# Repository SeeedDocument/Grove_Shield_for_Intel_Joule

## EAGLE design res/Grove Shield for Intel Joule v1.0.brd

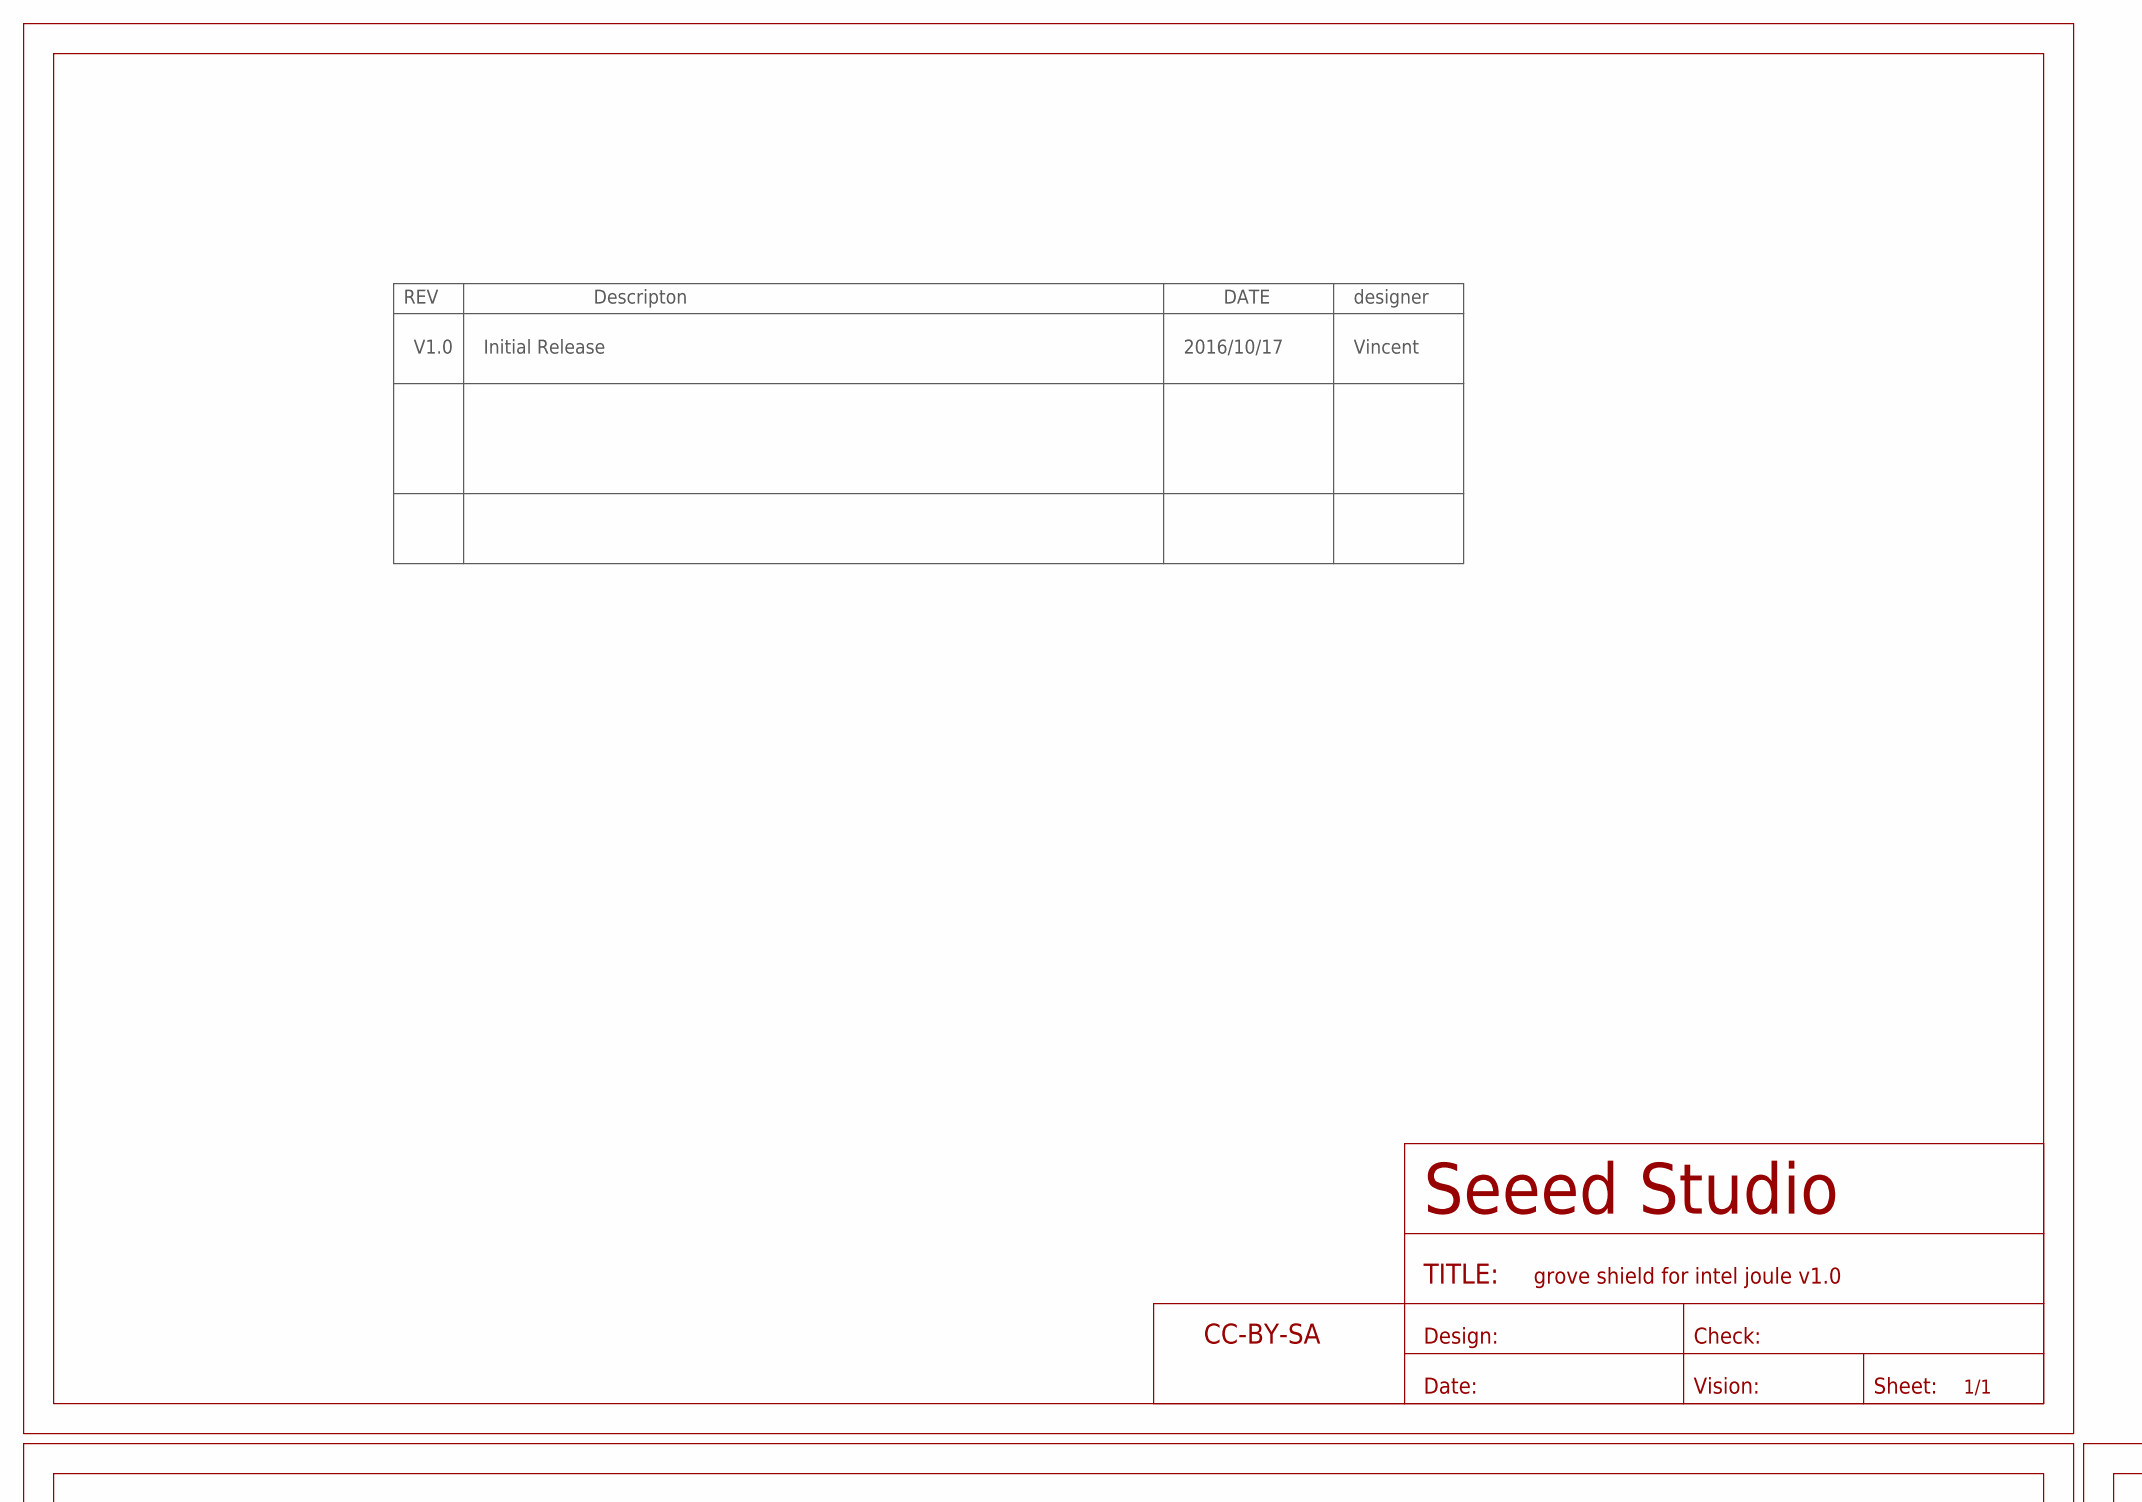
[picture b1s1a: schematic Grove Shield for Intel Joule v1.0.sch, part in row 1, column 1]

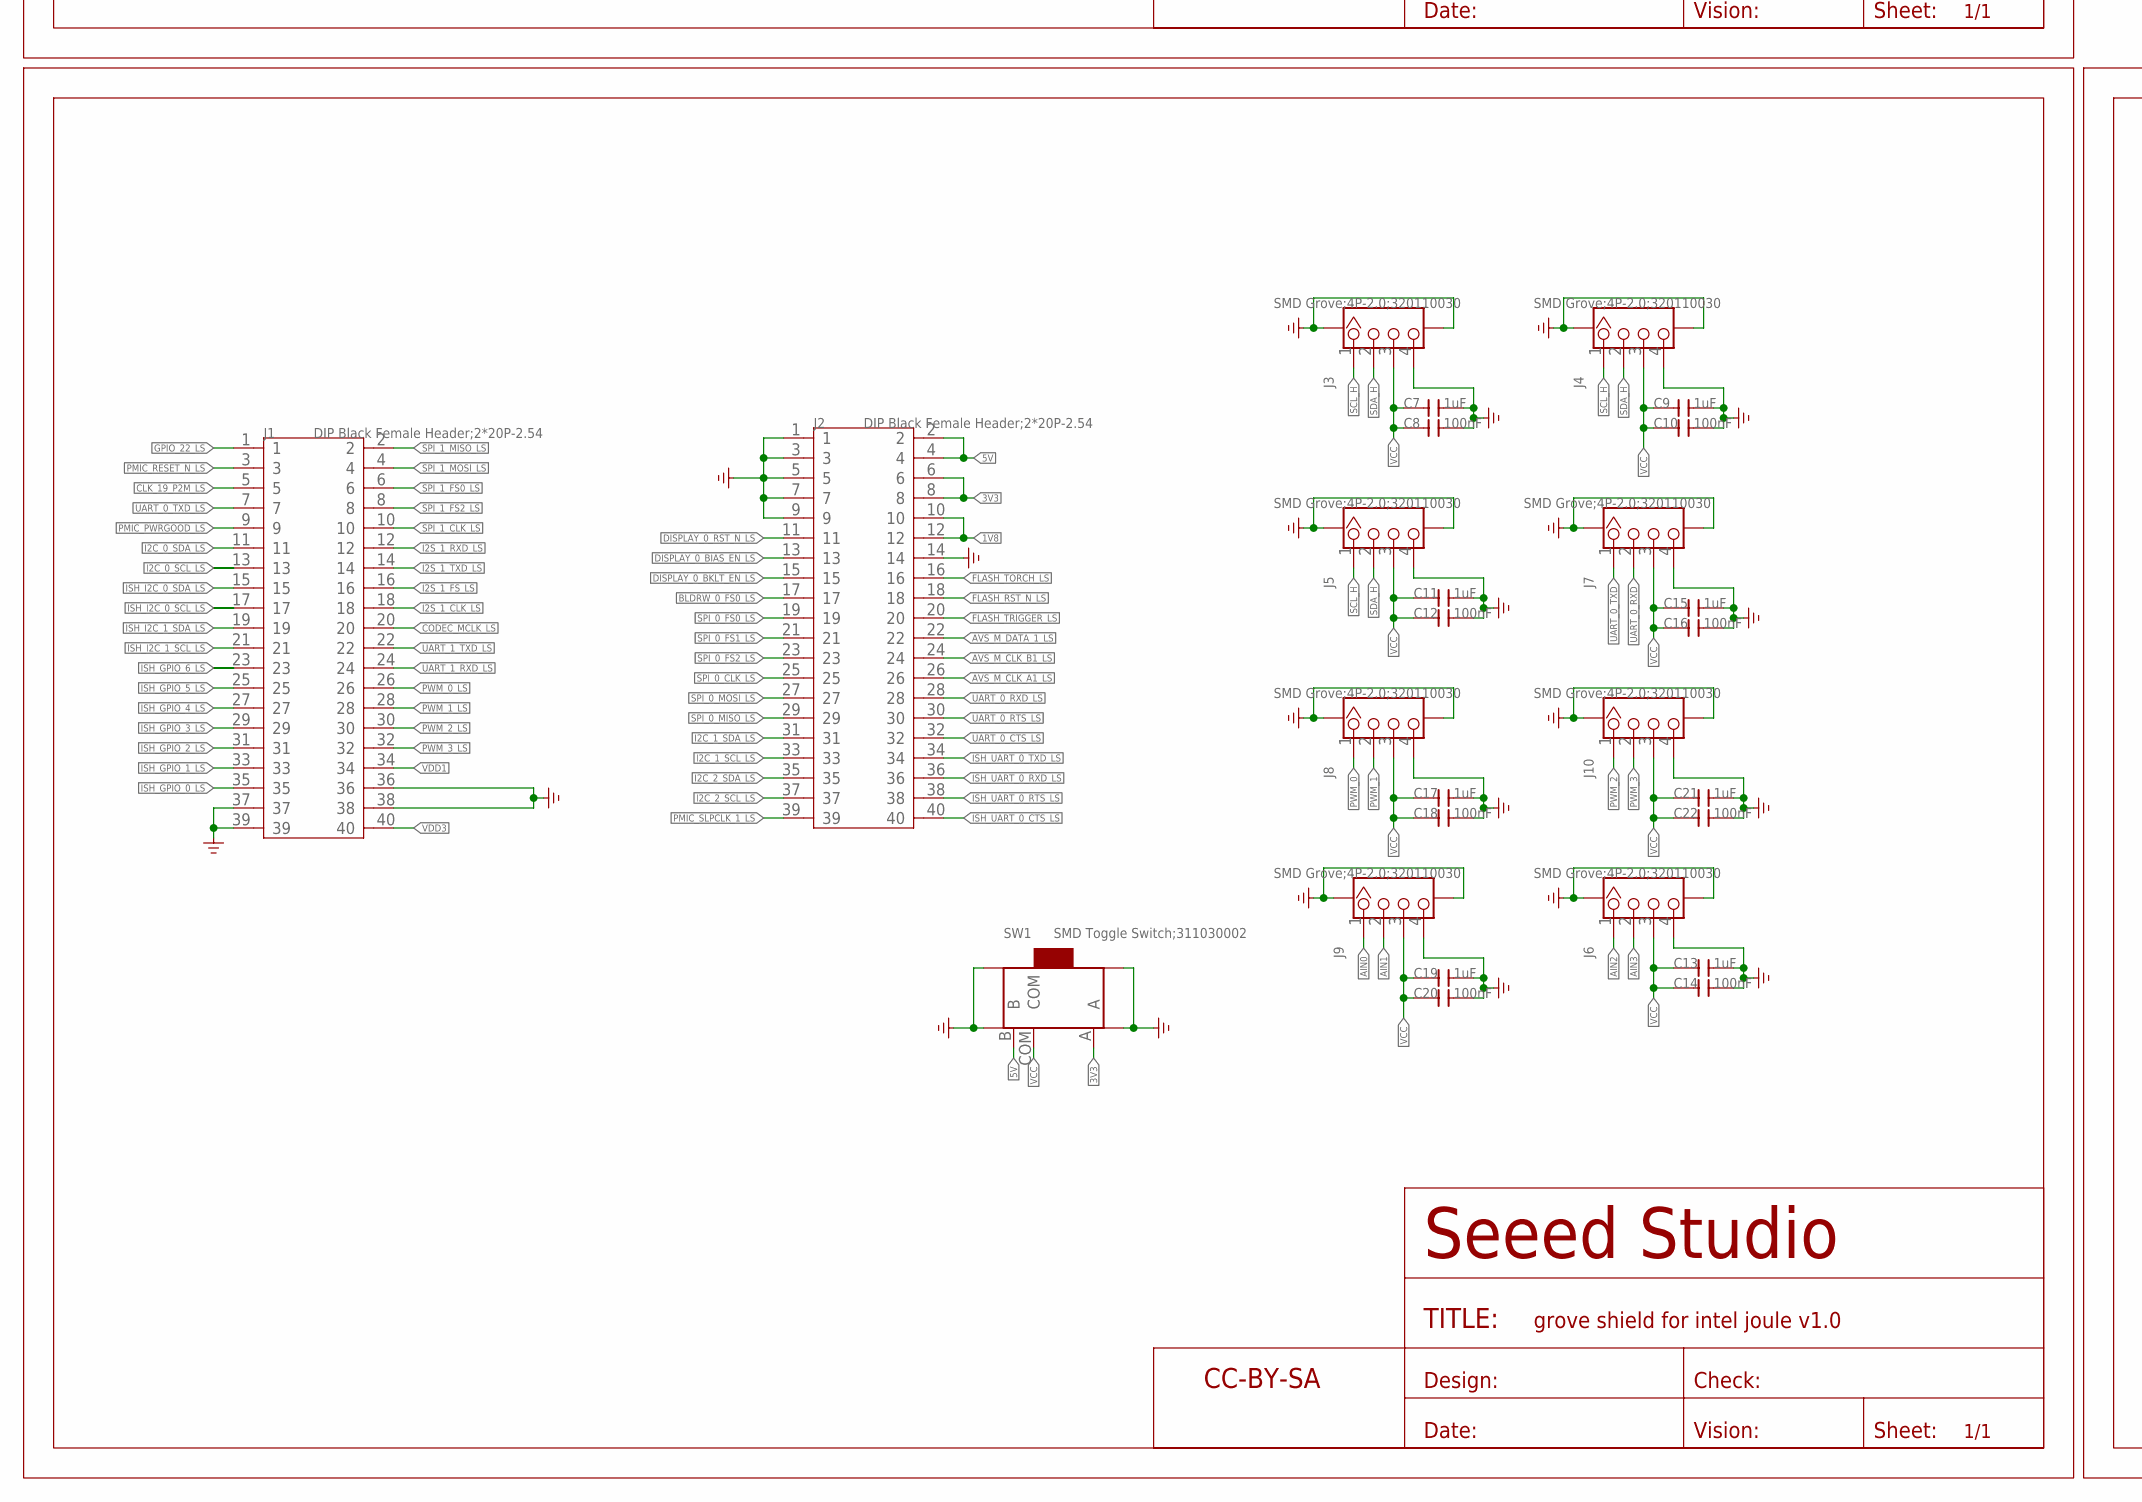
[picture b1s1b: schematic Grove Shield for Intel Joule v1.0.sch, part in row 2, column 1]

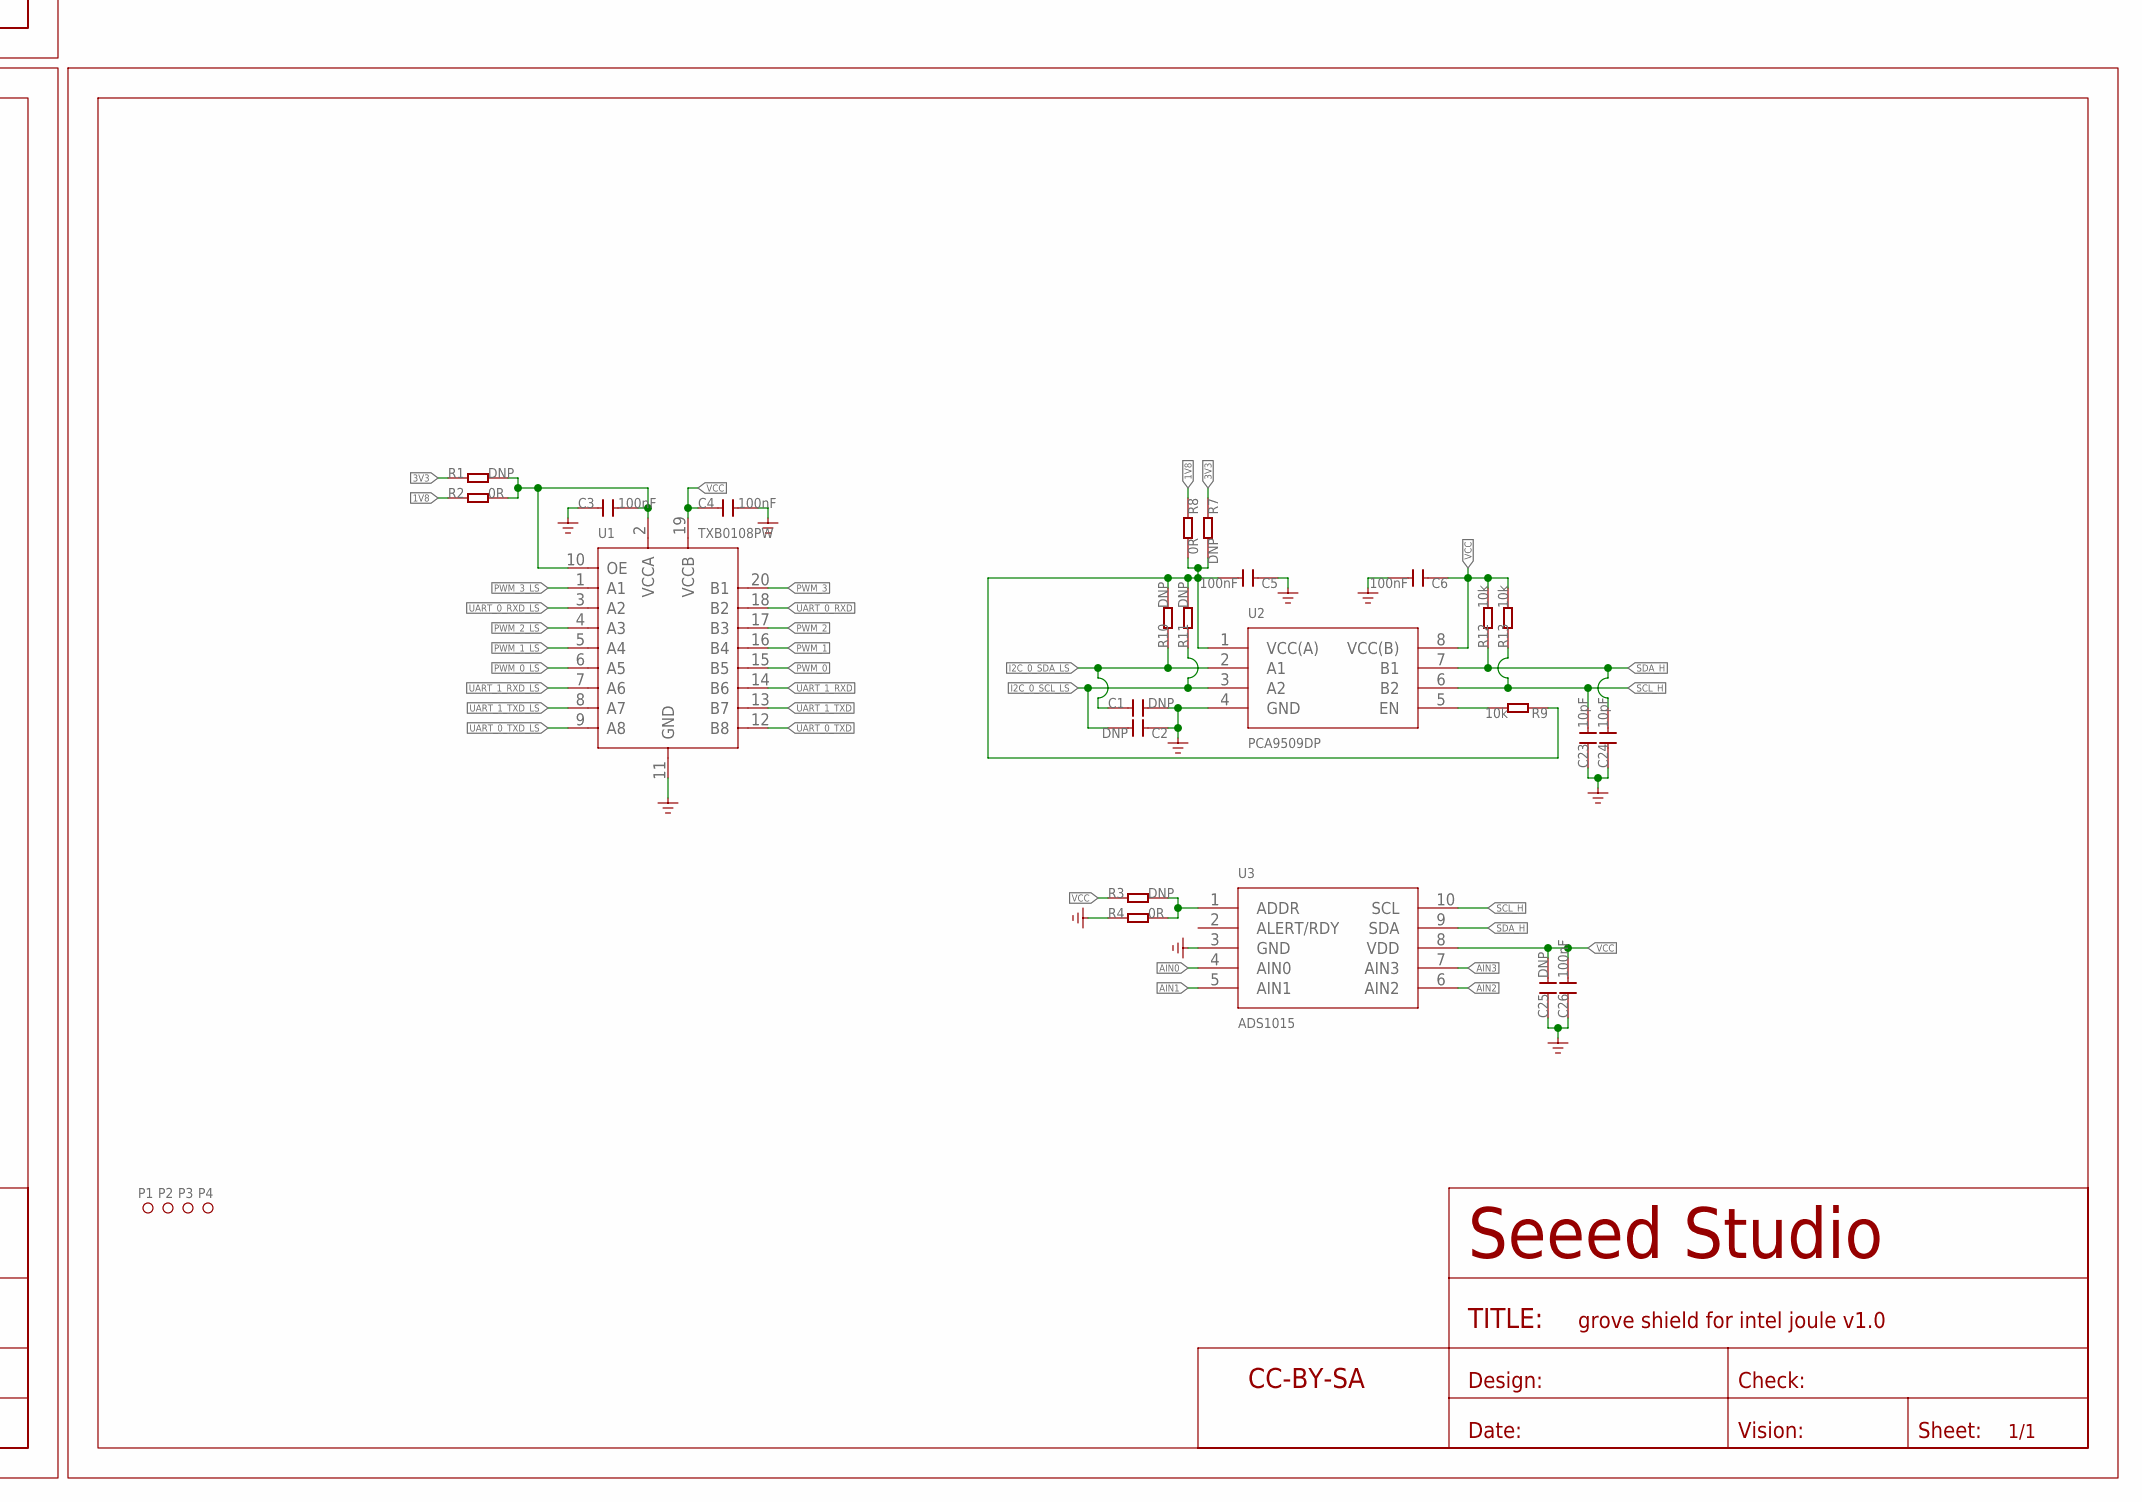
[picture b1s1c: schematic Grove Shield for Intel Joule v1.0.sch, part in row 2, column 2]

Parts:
C1, C2, C25: DNP; C0603
C3, C4, C5, C6, C8, C10, C12, C14, C16, C18, C20, C22, C26: 100nF; C0603
C7, C9, C11, C13, C15, C17, C19, C21: 1uF; C0603
C23, C24: 10pF; C0603
FR1, FR2, FR3: SEEEDSTUDIO-OPEN-SCH-FRAME; SEEEDSTUDIO-PCB-FRAME
J1, J2: DIP Black Female Header;2*20P-2.54; H2X20-2.54MM
J3, J4, J5, J6, J7, J8, J9, J10: SMD Grove;4P-2.0;320110030; HW4-SMD-2.0
P1, P2, P3, P4: MARK-1.0'ANNULAR'; ROUND-MARK-1.0
R1, R3, R7, R10, R11: DNP; R0603
R2, R4, R8: 0R; R0603
R9, R12, R13: 10k; R0603
SW1: SMD Toggle Switch;311030002; SW7-SMD-6.7X2.6X1.4MM-90D
U1: TXB0108PW; TSSOP20-0.65-6.5X4.4MM
U2: PCA9509DP; TSSOP8-0.65-3X3MM
U3: ADS1015; SSOP10-0.5-3X3MM

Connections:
1V8: J2.10, J2.12, R2.1, R8.1
3V3: J2.6, J2.8, R1.1, R7.1, SW1.A
5V: J2.2, J2.4, SW1.B
AIN0: J9.1, U3.4 (AIN0)
AIN1: J9.2, U3.5 (AIN1)
AIN2: J6.1, U3.6 (AIN2)
AIN3: J6.2, U3.7 (AIN3)
AVS_M_CLK_A1_LS: J2.26
AVS_M_CLK_B1_LS: J2.24
AVS_M_DATA_1_LS: J2.22
BLDRW_0_FS0_LS: J2.17
CLK_19_P2M_LS: J1.5
CODEC_MCLK_LS: J1.20
DISPLAY_0_BIAS_EN_LS: J2.13
DISPLAY_0_BKLT_EN_LS: J2.15
DISPLAY_0_RST_N_LS: J2.11
FLASH_RST_N_LS: J2.18
FLASH_TORCH_LS: J2.16
FLASH_TRIGGER_LS: J2.20
GND: C1.2, C2.1, C3.1, C4.2, C5.1, C6.2, C7.2, C8.2, C9.2, C10.2, C11.2, C12.2, C13.2, C14.2, C15.2, C16.2, C17.2, C18.2, C19.2, C20.2, C21.2, C22.2, C23.1, C24.1, C25.1, C26.1, J1.36, J1.37, J1.38, J1.39, J2.1, J2.3, J2.5, J2.7, J2.9, J2.14, J3.4, J3.SS1, J3.SS2, J4.4, J4.SS1, J4.SS2, J5.4, J5.SS1, J5.SS2, J6.4, J6.SS1, J6.SS2, J7.4, J7.SS1, J7.SS2, J8.4, J8.SS1, J8.SS2, J9.4, J9.SS1, J9.SS2, J10.4, J10.SS1, J10.SS2, R4.1, SW1.P1 (SS1), SW1.P2 (SS2), SW1.P3 (SS3), SW1.P4 (SS4), U1.11 (GND), U2.4 (GND), U3.3 (GND)
GPIO_22_LS: J1.1
I2C_0_SCL_LS: C2.2, J1.13, R11.1, U2.3 (A2)
I2C_0_SDA_LS: C1.1, J1.11, R10.1, U2.2 (A1)
I2C_1_SCL_LS: J2.33
I2C_1_SDA_LS: J2.31
I2C_2_SCL_LS: J2.37
I2C_2_SDA_LS: J2.35
I2S_1_CLK_LS: J1.18
I2S_1_FS_LS: J1.16
I2S_1_RXD_LS: J1.12
I2S_1_TXD_LS: J1.14
ISH_GPIO_0_LS: J1.35
ISH_GPIO_1_LS: J1.33
ISH_GPIO_2_LS: J1.31
ISH_GPIO_3_LS: J1.29
ISH_GPIO_4_LS: J1.27
ISH_GPIO_5_LS: J1.25
ISH_GPIO_6_LS: J1.23
ISH_I2C_0_SCL_LS: J1.17
ISH_I2C_0_SDA_LS: J1.15
ISH_I2C_1_SCL_LS: J1.21
ISH_I2C_1_SDA_LS: J1.19
ISH_UART_0_CTS_LS: J2.40
ISH_UART_0_RTS_LS: J2.38
ISH_UART_0_RXD_LS: J2.36
ISH_UART_0_TXD_LS: J2.34
unnamed: R9.2, U2.5 (EN)
unnamed: R3.2, R4.2, U3.1 (ADDR)
unnamed: C5.2, R7.2, R8.2, R9.1, R10.2, R11.2, U2.1 (VCC(A))
unnamed: C3.2, R1.2, R2.2, U1.2 (VCCA), U1.10 (OE)
PMIC_PWRGOOD_LS: J1.9
PMIC_RESET_N_LS: J1.3
PMIC_SLPCLK_1_LS: J2.39
PWM_0: J8.1, U1.15 (B5)
PWM_0_LS: J1.26, U1.6 (A5)
PWM_1: J8.2, U1.16 (B4)
PWM_1_LS: J1.28, U1.5 (A4)
PWM_2: J10.1, U1.17 (B3)
PWM_2_LS: J1.30, U1.4 (A3)
PWM_3: J10.2, U1.20 (B1)
PWM_3_LS: J1.32, U1.1 (A1)
SCL_H: C23.2, J3.1, J4.1, J5.1, R13.1, U2.6 (B2), U3.10 (SCL)
SDA_H: C24.2, J3.2, J4.2, J5.2, R12.1, U2.7 (B1), U3.9 (SDA)
SPI_0_CLK_LS: J2.25
SPI_0_FS0_LS: J2.19
SPI_0_FS1_LS: J2.21
SPI_0_FS2_LS: J2.23
SPI_0_MISO_LS: J2.29
SPI_0_MOSI_LS: J2.27
SPI_1_CLK_LS: J1.10
SPI_1_FS0_LS: J1.6
SPI_1_FS2_LS: J1.8
SPI_1_MISO_LS: J1.2
SPI_1_MOSI_LS: J1.4
UART_0_CTS_LS: J2.32
UART_0_RTS_LS: J2.30
UART_0_RXD: J7.2, U1.18 (B2)
UART_0_RXD_LS: J2.28, U1.3 (A2)
UART_0_TXD: J7.1, U1.12 (B8)
UART_0_TXD_LS: J1.7, U1.9 (A8)
UART_1_RXD: U1.14 (B6)
UART_1_RXD_LS: J1.24, U1.7 (A6)
UART_1_TXD: U1.13 (B7)
UART_1_TXD_LS: J1.22, U1.8 (A7)
VCC: C4.1, C6.1, C7.1, C8.1, C9.1, C10.1, C11.1, C12.1, C13.1, C14.1, C15.1, C16.1, C17.1, C18.1, C19.1, C20.1, C21.1, C22.1, C25.2, C26.2, J3.3, J4.3, J5.3, J6.3, J7.3, J8.3, J9.3, J10.3, R3.1, R12.2, R13.2, SW1.COM, U1.19 (VCCB), U2.8 (VCC(B)), U3.8 (VDD)
VDD1: J1.34
VDD3: J1.40

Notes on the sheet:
REV
Descripton
DATE
designer
V1.0
Initial Release
2016/10/17
Vincent

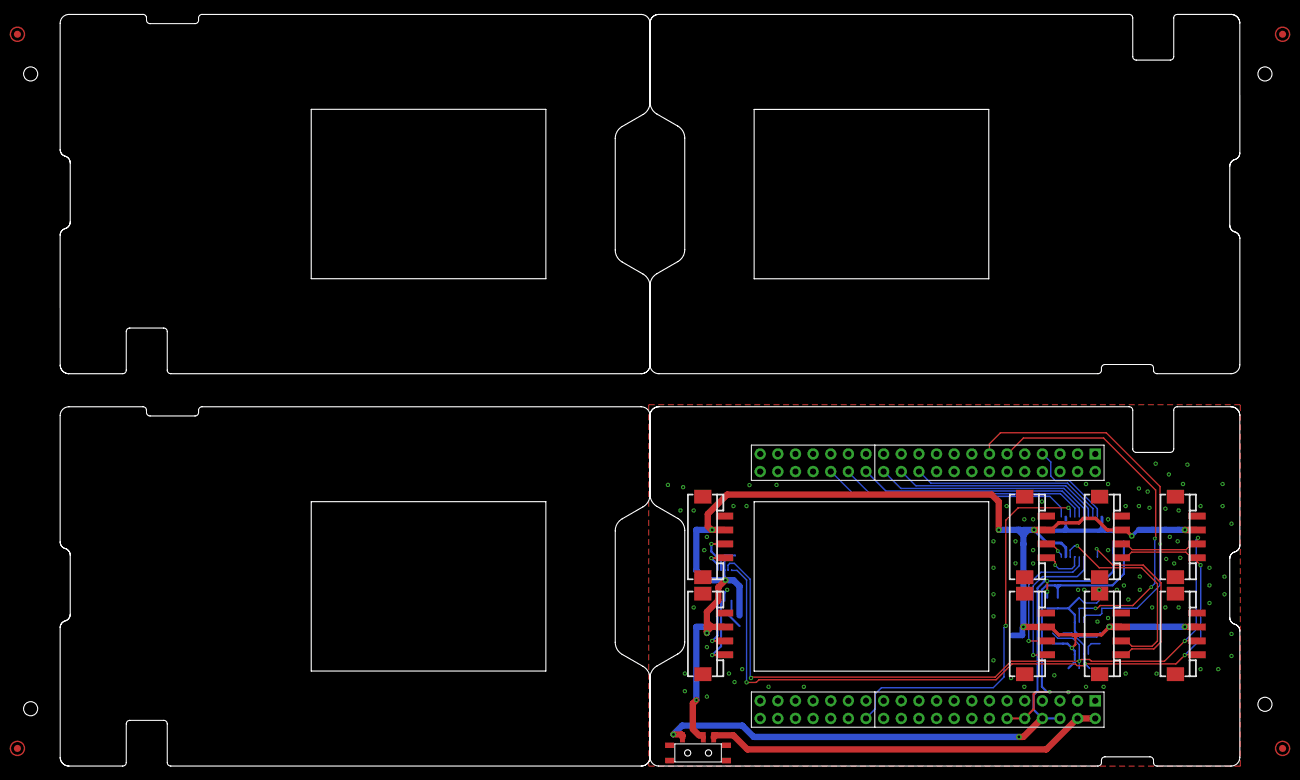
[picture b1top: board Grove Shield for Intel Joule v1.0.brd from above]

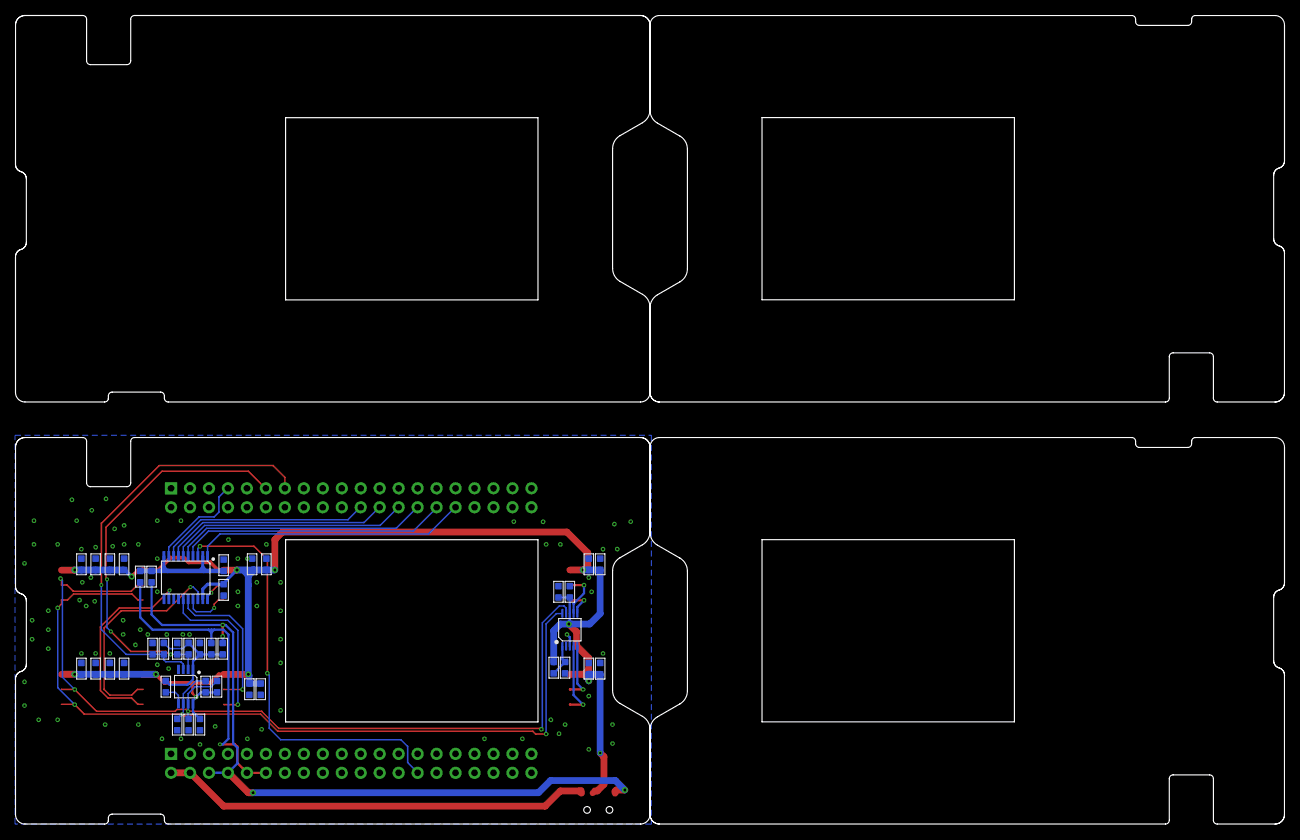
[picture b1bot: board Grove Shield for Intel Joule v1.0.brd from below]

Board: 2 copper layers, 169.9 x 108.3 mm, 58 parts (40 on the bottom side), 31 nets.

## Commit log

2016-12-27 init
2016-12-28 finish v0.1
2016-12-28 edit 2.png
2016-12-29 add hardware overview pic
2016-12-29 add hardware overview
2016-12-30 update by loovee
2017-05-09 update pin information

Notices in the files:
parts and their libraries:
moudle-new: This work is licensed under the Creative Commons Attribution 4.0 International License.
To view a copy of this license,visit:
http://creativecommons.org/licenses/by-sa/4.0
moudle-new: CC-BY-SA
